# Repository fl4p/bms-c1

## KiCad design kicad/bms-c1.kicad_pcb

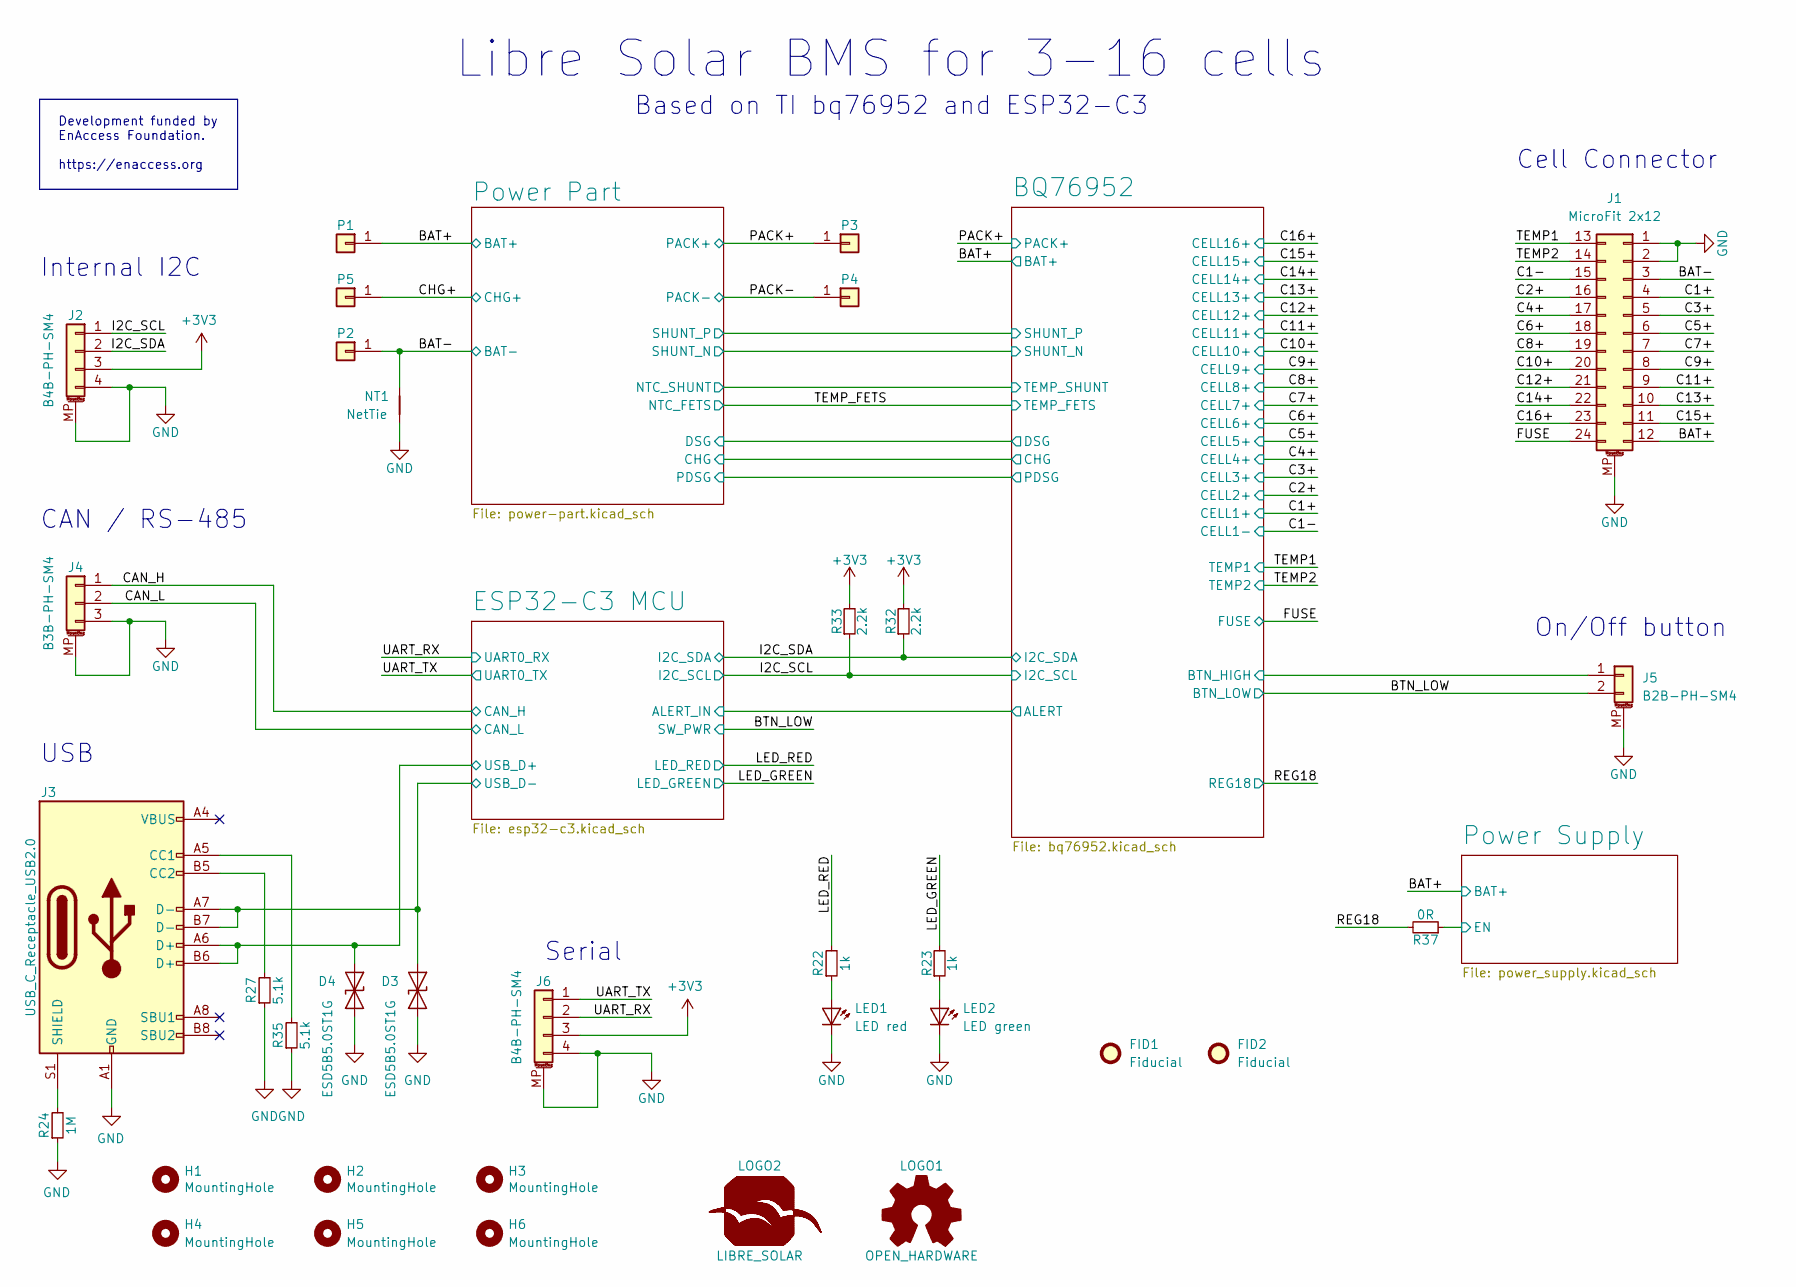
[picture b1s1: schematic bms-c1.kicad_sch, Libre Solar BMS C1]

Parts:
D3, D4: ESD5B5.0ST1G; D_SOD-523; PartNumber ESD5B5.0ST1G; LCSC C93623
FID1, FID2: Fiducial; Fiducial_1mm_Mask2mm
H1, H2, H3, H4, H5, H6: MountingHole; MountingHole_3.2mm_M3_Pad_TopBottom
J1: MicroFit 2x12; Molex_Micro-Fit_3.0_43045-2410_2x12-1MP_P3.00mm_Horizontal; PartNumber 662024231722
J2, J6: B4B-PH-SM4; JST_PH_B4B-PH-SM4-TB_1x04-1MP_P2.00mm_Vertical; PartNumber B4B-PH-SM4-TB(LF)(SN); LCSC C160354
J3: USB_C_Receptacle_USB2.0; USB_C_Receptacle_GCT_USB4105-xx-A_16P_TopMnt_Horizontal; PartNumber USB4105-GF-A
J4: B3B-PH-SM4; JST_PH_B3B-PH-SM4-TB_1x03-1MP_P2.00mm_Vertical; PartNumber B3B-PH-SM4-TB(LF)(SN); LCSC C160353
J5: B2B-PH-SM4; JST_PH_B2B-PH-SM4-TB_1x02-1MP_P2.00mm_Vertical; PartNumber B2B-PH-SM4-TB(LF)(SN); LCSC C160352
LED1: LED red; LED_0603_1608Metric; PartNumber LTST-C190KRKT; LCSC C94869
LED2: LED green; LED_0603_1608Metric; PartNumber LTST-C190KGKT; LCSC C125094
LOGO1: OPEN_HARDWARE; OSHW-Logo_5.7x6mm_SilkScreen
LOGO2: LIBRE_SOLAR; LIBRESOLAR_LOGO
NT1: NetTie; NetTie-2_SMD_Pad0.5mm
P1, P2, P3, P4: CONN_01X01; Wuerth_PowerPlus_M5_Nut; PartNumber 225852-E; LCSC C3217898
P5: CONN_01X01; SolderWirePad_1x01_SMD_5x10mm
R22, R23: 1k; R_0603_1608; PartNumber RC0603FR-071KL
R24: 1M; R_0603_1608; PartNumber RC0603FR-071ML
R27, R35: 5.1k; R_0603_1608; PartNumber RC0603FR-075K1L
R32, R33: 2.2k; R_0603_1608; PartNumber RC0603FR-072K2L
R37: 0R; R_0603_1608; PartNumber RC0603FR-070RL

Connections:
+3V3: J2.3, J6.3, R32.2, R33.2; also elsewhere on the board
/BAT+: J1.12, P1.1; also elsewhere on the board
/BAT-: J1.3, NT1.1, P2.1; also elsewhere on the board
/BQ76952/BTN_HIGH: J5.1; also elsewhere on the board
/BTN_LOW: J5.2; also elsewhere on the board
/C1+: J1.4; also elsewhere on the board
/C1-: J1.15; also elsewhere on the board
/C2+: J1.16; also elsewhere on the board
/C3+: J1.5; also elsewhere on the board
/C4+: J1.17; also elsewhere on the board
/C5+: J1.6; also elsewhere on the board
/C6+: J1.18; also elsewhere on the board
/C7+: J1.7; also elsewhere on the board
/C8+: J1.19; also elsewhere on the board
/C9+: J1.8; also elsewhere on the board
/C10+: J1.20; also elsewhere on the board
/C11+: J1.9; also elsewhere on the board
/C12+: J1.21; also elsewhere on the board
/C13+: J1.10; also elsewhere on the board
/C14+: J1.22; also elsewhere on the board
/C15+: J1.11; also elsewhere on the board
/C16+: J1.23; also elsewhere on the board
/CAN_H: J4.1; also elsewhere on the board
/CAN_L: J4.2; also elsewhere on the board
/CHG+: P5.1; also elsewhere on the board
/ESP32-C3 MCU/USB_D+: D4.2 (A2), J3.A6 (D+), J3.B6 (D+); also elsewhere on the board
/ESP32-C3 MCU/USB_D-: D3.2 (A2), J3.A7 (D-), J3.B7 (D-); also elsewhere on the board
/FUSE: J1.24; also elsewhere on the board
/I2C_SCL: J2.1, R33.1; also elsewhere on the board
/I2C_SDA: J2.2, R32.1; also elsewhere on the board
/LED_GREEN: R23.2; also elsewhere on the board
/LED_RED: R22.2; also elsewhere on the board
/PACK+: P3.1; also elsewhere on the board
/PACK-: P4.1; also elsewhere on the board
/Power Supply/EN: R37.1; also elsewhere on the board
/REG18: R37.2; also elsewhere on the board
/TEMP1: J1.13; also elsewhere on the board
/TEMP2: J1.14; also elsewhere on the board
/UART_RX: J6.2; also elsewhere on the board
/UART_TX: J6.1; also elsewhere on the board
GND: D3.1 (A1), D4.1 (A1), J1.1, J1.2, J1.MP (MountPin), J2.4, J2.MP (MountPin), J3.A1 (GND), J3.A12 (GND), J3.B1 (GND), J3.B12 (GND), J4.3, J4.MP (MountPin), J5.MP (MountPin), J6.4, J6.MP (MountPin), LED1.1 (K), LED2.1 (K), NT1.2, R24.1, R27.1, R35.1; also elsewhere on the board
unnamed: J3.A5 (CC1), R35.2
unnamed: J3.B5 (CC2), R27.2
unnamed: J3.S1 (SHIELD), R24.2
unnamed: LED1.2 (A), R22.1
unnamed: LED2.2 (A), R23.1

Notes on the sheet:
Based on TI bq76952 and ESP32-C3
CAN / RS-485
Development funded by EnAccess Foundation. https://enaccess.org
USB
Serial
Libre Solar BMS for 3-16 cells
Cell Connector
Internal I2C
On/Off button

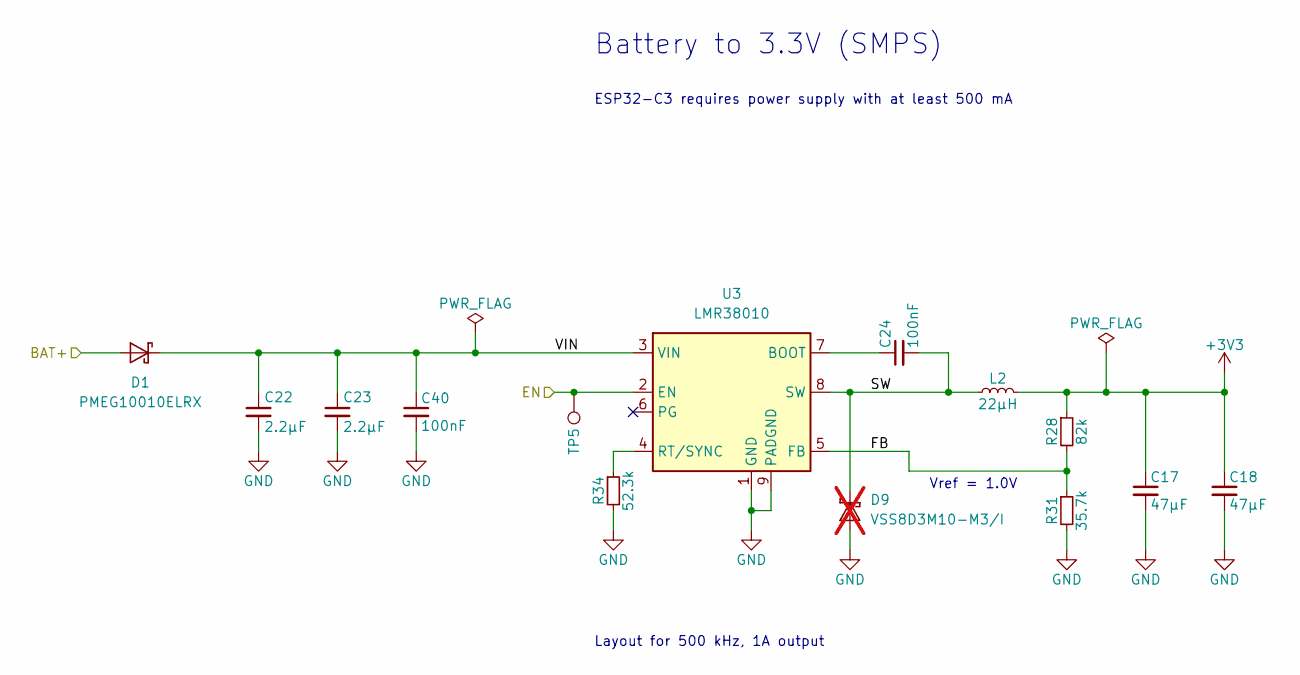
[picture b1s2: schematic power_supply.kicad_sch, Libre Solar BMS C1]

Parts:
C17, C18: 47µF; C_1210_3225; PartNumber CL32B476MPJNNNE; LCSC C525654
C22, C23: 2.2µF; C_1210_3225; PartNumber CL32B225KCJSNNE; LCSC C55151
C24, C40: 100nF; C_0603_1608; PartNumber CL10B104KC8NNNC; LCSC C15725
D1: PMEG10010ELRX; D_SOD-123F; PartNumber PMEG10010ELRX; LCSC C179426
D9: VSS8D3M10-M3/I; D_SOD-128; PartNumber VSS8D3M10-M3/H; LCSC C3760174; not fitted
L2: 22µH; Bourns_SRN8040TA; PartNumber SRN8040-220M; LCSC C92946
R28: 82k; R_0603_1608; PartNumber RC0603FR-0782KL
R31: 35.7k; R_0603_1608; PartNumber RC0603FR-0735K7L
R34: 52.3k; R_0603_1608; PartNumber RC0603FR-0752K3L
TP5: TestPoint; TestPoint_Pad_D1.5mm
U3: LMR38010; SOIC-8-1EP_3.9x4.9mm_P1.27mm_EP2.4x3.1mm_ThermalVias; PartNumber LMR38010SDDAR; LCSC C3192337

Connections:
+3V3: C17.1, C18.1, L2.2, R28.1; also elsewhere on the board
/BAT+: D1.2 (A); also elsewhere on the board
/Power Supply/EN: TP5.1, U3.2 (EN); also elsewhere on the board
/Power Supply/FB: R28.2, R31.1, U3.5 (FB)
/Power Supply/SW: C24.2, D9.1 (K), L2.1, U3.8 (SW)
/Power Supply/VIN: C22.1, C23.1, C40.1, D1.1 (K), U3.3 (VIN)
GND: C17.2, C18.2, C22.2, C23.2, C40.2, D9.2 (A), R31.2, R34.2, U3.1 (GND), U3.9 (PADGND); also elsewhere on the board
unnamed: C24.1, U3.7 (BOOT)
unnamed: R34.1, U3.4 (RT/SYNC)

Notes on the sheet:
ESP32-C3 requires power supply with at least 500 mA
Layout for 500 kHz, 1A output
Battery to 3.3V (SMPS)
Vref = 1.0V

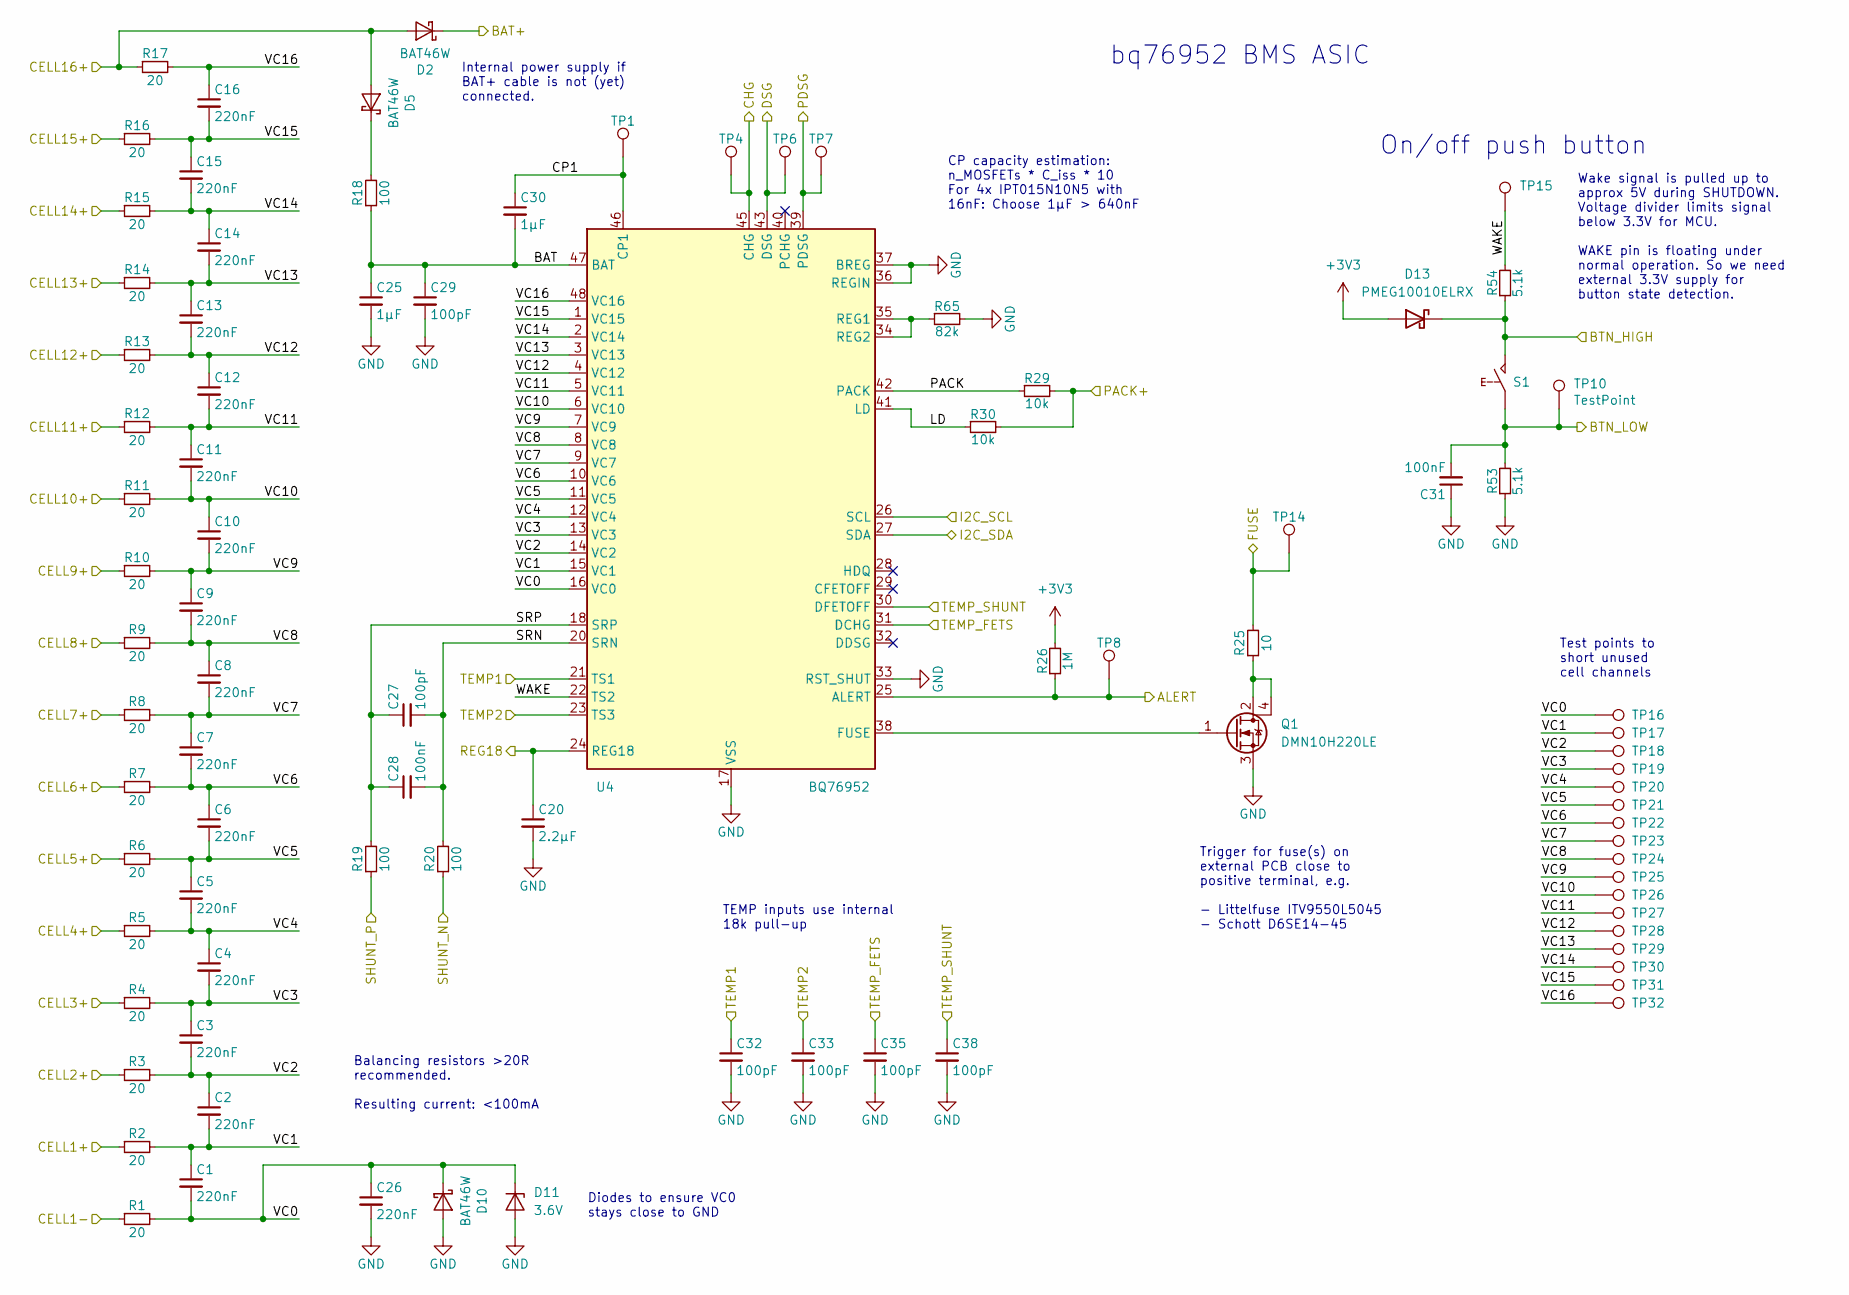
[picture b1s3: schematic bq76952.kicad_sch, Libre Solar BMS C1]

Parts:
C1, C2, C3, C4, C5, C6, C7, C8, C9, C10, C11, C12, C13, C14, C15, C16, C26: 220nF; C_0603_1608; PartNumber CL10B224KA8NNNC; LCSC C21120
C20: 2.2µF; C_0603_1608; PartNumber CL10A225KP8NNNC; LCSC C1607
C25: 1µF; C_1206_3216; PartNumber CL31B105KCHNNNE; LCSC C13832
C27, C29, C32, C33, C35, C38: 100pF; C_0603_1608; PartNumber CL10C101JC8NNNC; LCSC C296717
C28, C31: 100nF; C_0603_1608; PartNumber CL10B104KC8NNNC; LCSC C15725
C30: 1µF; C_0603_1608; PartNumber CL10A105KA8NNNC; LCSC C5673
D2, D5, D10: BAT46W; D_SOD-123; PartNumber BAT46W-7-F; LCSC C83152
D11: 3.6V; D_SOD-123; PartNumber MMSZ4685T1G; LCSC C66886
D13: PMEG10010ELRX; D_SOD-123F; PartNumber PMEG10010ELRX; LCSC C179426
Q1: DMN10H220LE; SOT-223; PartNumber DMN10H220LE; LCSC C258216
R1, R2, R3, R4, R5, R6, R7, R8, R9, R10, R11, R12, R13, R14, R15, R16, R17: 20; R_2010_5025; PartNumber RC2010JK-0720RL; LCSC C163344
R18: 100; R_1206_3216; PartNumber RC1206FR-07100RL
R19, R20: 100; R_0603_1608; PartNumber RC0603FR-07100RL
R25: 10; R_1206_3216; PartNumber RC1206FR-0710RL
R26: 1M; R_0603_1608; PartNumber RC0603FR-071ML
R29, R30: 10k; R_0603_1608; PartNumber RC0603FR-0710KL
R53, R54: 5.1k; R_0603_1608; PartNumber RC0603FR-075K1L
R65: 82k; R_0603_1608; PartNumber RC0603FR-0782KL
S1: SW_PUSH; SW_SPST_TL3305A; PartNumber TL3305AF160QG; LCSC C2886899
TP1, TP4, TP6, TP7, TP8, TP10, TP14, TP15: TestPoint; TestPoint_Pad_D1.5mm
TP16, TP17, TP18, TP19, TP20, TP21, TP22, TP23, TP24, TP25, TP26, TP27, TP28, TP29, TP30, TP31, TP32: TestPoint; TestPoint_Pad_1.0x1.0mm
U4: BQ76952; TQFP-48_7x7mm_P0.5mm; PartNumber BQ76952PFBR; LCSC C2862742

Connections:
+3V3: D13.2 (A), R26.2; also elsewhere on the board
/BAT+: D2.1 (K); also elsewhere on the board
/BQ76952/ALERT: R26.1, TP8.1, U4.25 (ALERT); also elsewhere on the board
/BQ76952/BAT: C25.1, C29.1, C30.2, R18.1, U4.47 (BAT)
/BQ76952/BTN_HIGH: D13.1 (K), R54.1, S1.2; also elsewhere on the board
/BQ76952/CHG: TP4.1, U4.45 (CHG); also elsewhere on the board
/BQ76952/CP1: C30.1, TP1.1, U4.46 (CP1)
/BQ76952/DSG: TP6.1, U4.43 (DSG); also elsewhere on the board
/BQ76952/LD: R30.1, U4.41 (LD)
/BQ76952/PACK: R29.1, U4.42 (PACK)
/BQ76952/PDSG: TP7.1, U4.39 (PDSG); also elsewhere on the board
/BQ76952/SHUNT_N: R20.1; also elsewhere on the board
/BQ76952/SHUNT_P: R19.1; also elsewhere on the board
/BQ76952/SRN: C27.2, C28.2, R20.2, U4.20 (SRN)
/BQ76952/SRP: C27.1, C28.1, R19.2, U4.18 (SRP)
/BQ76952/TEMP_SHUNT: C38.1, U4.30 (DFETOFF); also elsewhere on the board
/BQ76952/VC0: C1.2, C26.1, D10.1 (K), D11.1 (K), R1.2, TP16.1, U4.16 (VC0)
/BQ76952/VC1: C1.1, C2.2, R2.2, TP17.1, U4.15 (VC1)
/BQ76952/VC2: C2.1, C3.2, R3.2, TP18.1, U4.14 (VC2)
/BQ76952/VC3: C3.1, C4.2, R4.2, TP19.1, U4.13 (VC3)
/BQ76952/VC4: C4.1, C5.2, R5.2, TP20.1, U4.12 (VC4)
/BQ76952/VC5: C5.1, C6.2, R6.2, TP21.1, U4.11 (VC5)
/BQ76952/VC6: C6.1, C7.2, R7.2, TP22.1, U4.10 (VC6)
/BQ76952/VC7: C7.1, C8.2, R8.2, TP23.1, U4.9 (VC7)
/BQ76952/VC8: C8.1, C9.2, R9.2, TP24.1, U4.8 (VC8)
/BQ76952/VC9: C9.1, C10.2, R10.2, TP25.1, U4.7 (VC9)
/BQ76952/VC10: C10.1, C11.2, R11.2, TP26.1, U4.6 (VC10)
/BQ76952/VC11: C11.1, C12.2, R12.2, TP27.1, U4.5 (VC11)
/BQ76952/VC12: C12.1, C13.2, R13.2, TP28.1, U4.4 (VC12)
/BQ76952/VC13: C13.1, C14.2, R14.2, TP29.1, U4.3 (VC13)
/BQ76952/VC14: C14.1, C15.2, R15.2, TP30.1, U4.2 (VC14)
/BQ76952/VC15: C15.1, C16.2, R16.2, TP31.1, U4.1 (VC15)
/BQ76952/VC16: C16.1, R17.2, TP32.1, U4.48 (VC16)
/BQ76952/WAKE: R54.2, TP15.1, U4.22 (TS2)
/BTN_LOW: C31.2, R53.2, S1.1, TP10.1; also elsewhere on the board
/C1+: R2.1; also elsewhere on the board
/C1-: R1.1; also elsewhere on the board
/C2+: R3.1; also elsewhere on the board
/C3+: R4.1; also elsewhere on the board
/C4+: R5.1; also elsewhere on the board
/C5+: R6.1; also elsewhere on the board
/C6+: R7.1; also elsewhere on the board
/C7+: R8.1; also elsewhere on the board
/C8+: R9.1; also elsewhere on the board
/C9+: R10.1; also elsewhere on the board
/C10+: R11.1; also elsewhere on the board
/C11+: R12.1; also elsewhere on the board
/C12+: R13.1; also elsewhere on the board
/C13+: R14.1; also elsewhere on the board
/C14+: R15.1; also elsewhere on the board
/C15+: R16.1; also elsewhere on the board
/C16+: D2.2 (A), D5.2 (A), R17.1; also elsewhere on the board
/FUSE: R25.2, TP14.1; also elsewhere on the board
/I2C_SCL: U4.26 (SCL); also elsewhere on the board
/I2C_SDA: U4.27 (SDA); also elsewhere on the board
/PACK+: R29.2, R30.2; also elsewhere on the board
/REG18: C20.1, U4.24 (REG18); also elsewhere on the board
/TEMP1: C32.1, U4.21 (TS1); also elsewhere on the board
/TEMP2: C33.1, U4.23 (TS3); also elsewhere on the board
/TEMP_FETS: C35.1, U4.31 (DCHG); also elsewhere on the board
GND: C20.2, C25.2, C26.2, C29.2, C31.1, C32.2, C33.2, C35.2, C38.2, D10.2 (A), D11.2 (A), Q1.3 (S), R53.1, R65.2, U4.17 (VSS), U4.33 (RST_SHUT), U4.36 (REGIN), U4.37 (BREG); also elsewhere on the board
unnamed: D5.1 (K), R18.2
unnamed: Q1.2 (D), Q1.4 (D), R25.1
unnamed: Q1.1 (G), U4.38 (FUSE)
unnamed: R65.1, U4.34 (REG2), U4.35 (REG1)

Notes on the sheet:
TEMP inputs use internal 18k pull-up
CP capacity estimation: n_MOSFETs * C_iss * 10 For 4x IPT015N10N5 with 16nF: Choose 1µF > 640nF
bq76952 BMS ASIC
Wake signal is pulled up to approx 5V during SHUTDOWN. Voltage divider limits signal below 3.3V for MCU. WAKE pin is floating under normal operation. So we need external 3.3V supply for button state detection.
On/off push button
Trigger for fuse(s) on external PCB close to positive terminal, e.g. - Littelfuse ITV9550L5045 - Schott D6SE14-45
Balancing resistors >20R recommended. Resulting current: <100mA
Test points to short unused cell channels
Internal power supply if BAT+ cable is not (yet) connected.
Diodes to ensure VC0 stays close to GND

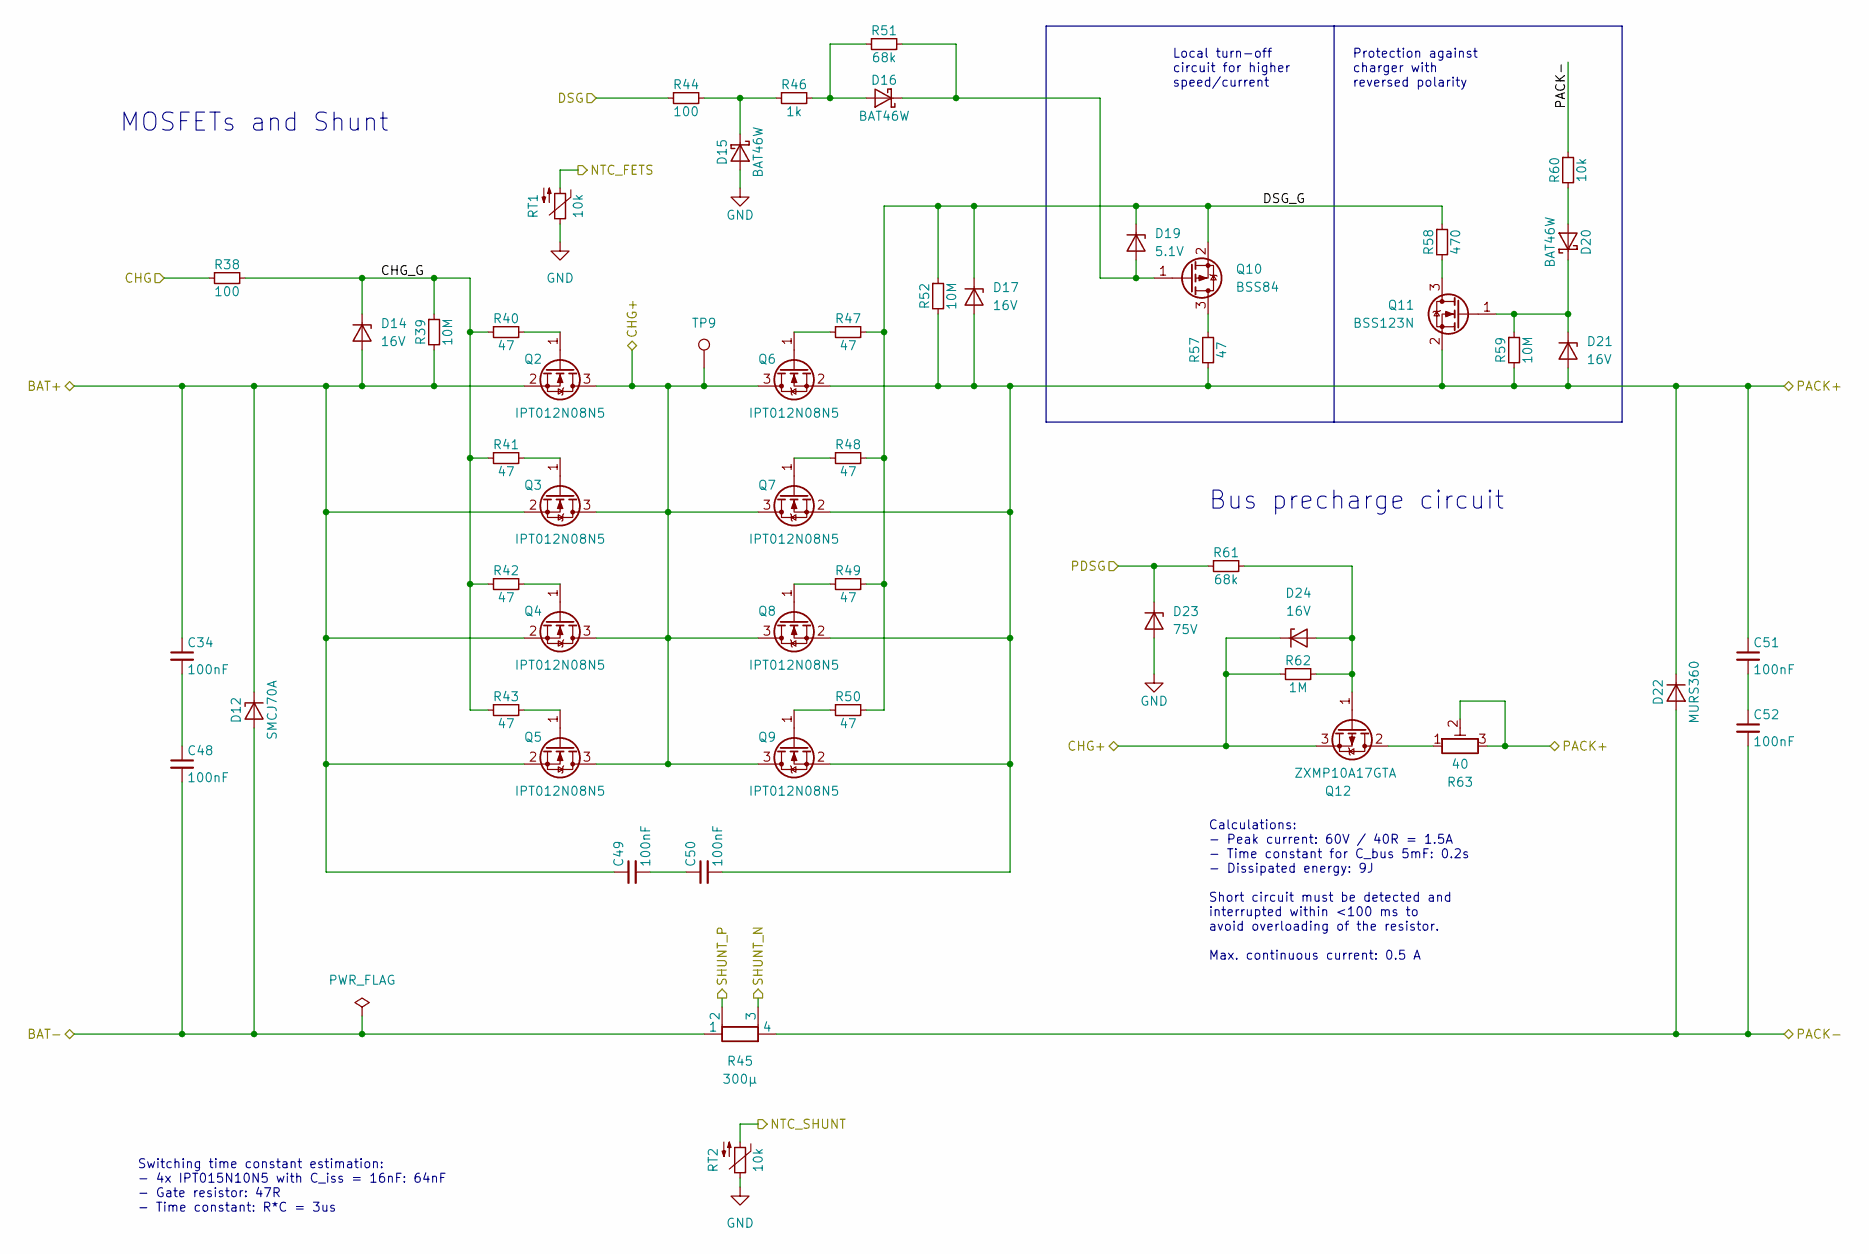
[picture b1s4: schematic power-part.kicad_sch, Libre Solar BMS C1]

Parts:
C34, C48, C49, C50, C51, C52: 100nF; C_0603_1608; PartNumber CL10B104KC8NNNC; LCSC C15725
D12: SMCJ70A; D_SMC; PartNumber SMCJ70A; LCSC C135194
D14, D17, D21, D24: 16V; D_SOD-123; PartNumber MMSZ5246B-7-F; LCSC C282317
D15, D16, D20: BAT46W; D_SOD-123; PartNumber BAT46W-7-F; LCSC C83152
D19: 5.1V; D_SOD-323; PartNumber BZT52C5V1S-7-F; LCSC C151348
D22: MURS360; D_SMC; PartNumber MURS360; LCSC C388245
D23: 75V; D_SOD-123; PartNumber MMSZ5267BT1G; LCSC C266795
Q2, Q3, Q4, Q5, Q6, Q7, Q8, Q9: IPT012N08N5; Infineon_PG-HSOF-8-1_ThermalVias; PartNumber IPT012N08N5; LCSC C531199
Q10: BSS84; SOT-23; PartNumber BSS84AK,215; LCSC C127273
Q11: BSS123N; SOT-23; PartNumber BSS123N H6327; LCSC C534594
Q12: ZXMP10A17GTA; SOT-223-3_TabPin2; PartNumber ZXMP10A17GTA; LCSC C32998
R38, R44: 100; R_0603_1608; PartNumber RC0603FR-07100RL
R39, R52, R59: 10M; R_0603_1608; PartNumber RC0603FR-0710ML
R40, R41, R42, R43, R47, R48, R49, R50, R57: 47; R_0603_1608; PartNumber RC0603FR-0747RL
R45: 300µ; R_Shunt_5931_Kelvin; PartNumber WSLP5931L3000FEA
R46: 1k; R_0603_1608; PartNumber RC0603FR-071KL
R51, R61: 68k; R_0603_1608; PartNumber RC0603FR-0768KL
R58: 470; R_0603_1608; PartNumber RC0603FR-07470RL
R60: 10k; R_0603_1608; PartNumber RC0603FR-0710KL
R62: 1M; R_0603_1608; PartNumber RC0603FR-071ML
R63: 40; Bourns_PWR163; PartNumber PWR163S-25-40R0FE
RT1, RT2: 10k; R_0603_1608; PartNumber NTCG163JF103FT1S; LCSC C406719
TP9: TestPoint; TestPoint_Pad_D1.5mm

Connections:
/BAT+: C34.1, C49.1, D12.1 (K), D14.2 (A), Q2.2 (S), Q3.2 (S), Q4.2 (S), Q5.2 (S), R39.2; also elsewhere on the board
/BAT-: C48.2, D12.2 (A), R45.1; also elsewhere on the board
/BQ76952/CHG: R38.1; also elsewhere on the board
/BQ76952/DSG: R44.1; also elsewhere on the board
/BQ76952/PDSG: D23.1 (K), R61.1; also elsewhere on the board
/BQ76952/SHUNT_N: R45.3; also elsewhere on the board
/BQ76952/SHUNT_P: R45.2; also elsewhere on the board
/BQ76952/TEMP_SHUNT: RT2.2; also elsewhere on the board
/CHG+: D24.1 (K), Q2.3 (D), Q3.3 (D), Q4.3 (D), Q5.3 (D), Q6.3 (D), Q7.3 (D), Q8.3 (D), Q9.3 (D), Q12.3 (S), R62.1, TP9.1; also elsewhere on the board
/PACK+: C50.2, C51.1, D17.2 (A), D21.2 (A), D22.1 (K), Q6.2 (S), Q7.2 (S), Q8.2 (S), Q9.2 (S), Q11.2 (S), R52.2, R57.1, R59.2, R63.2, R63.3; also elsewhere on the board
/PACK-: C52.2, D22.2 (A), R45.4, R60.1; also elsewhere on the board
/Power Part/CHG_G: D14.1 (K), R38.2, R39.1, R40.1, R41.1, R42.1, R43.1
/Power Part/DSG_G: D17.1 (K), D19.1 (K), Q10.2 (S), R47.2, R48.2, R49.2, R50.2, R52.1, R58.1
/TEMP_FETS: RT1.2; also elsewhere on the board
GND: D15.2 (A), D23.2 (A), RT1.1, RT2.1; also elsewhere on the board
unnamed: C34.2, C48.1
unnamed: C49.2, C50.1
unnamed: C51.2, C52.1
unnamed: D15.1 (K), R44.2, R46.1
unnamed: D16.2 (A), R46.2, R51.1
unnamed: D16.1 (K), D19.2 (A), Q10.1 (G), R51.2
unnamed: D20.2 (A), R60.2
unnamed: D20.1 (K), D21.1 (K), Q11.1 (G), R59.1
unnamed: D24.2 (A), Q12.1 (G), R61.2, R62.2
unnamed: Q2.1 (G), R40.2
unnamed: Q3.1 (G), R41.2
unnamed: Q4.1 (G), R42.2
unnamed: Q5.1 (G), R43.2
unnamed: Q6.1 (G), R47.1
unnamed: Q7.1 (G), R48.1
unnamed: Q8.1 (G), R49.1
unnamed: Q9.1 (G), R50.1
unnamed: Q10.3 (D), R57.2
unnamed: Q11.3 (D), R58.2
unnamed: Q12.2 (D), R63.1

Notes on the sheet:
Protection against charger with reversed polarity
Switching time constant estimation: - 4x IPT015N10N5 with C_iss = 16nF: 64nF - Gate resistor: 47R - Time constant: R*C = 3us
MOSFETs and Shunt
Local turn-off circuit for higher speed/current
Bus precharge circuit
Calculations: - Peak current: 60V / 40R = 1.5A - Time constant for C_bus 5mF: 0.2s - Dissipated energy: 9J Short circuit must be detected and interrupted within <100 ms to avoid overloading of the resistor. Max. continuous current: 0.5 A

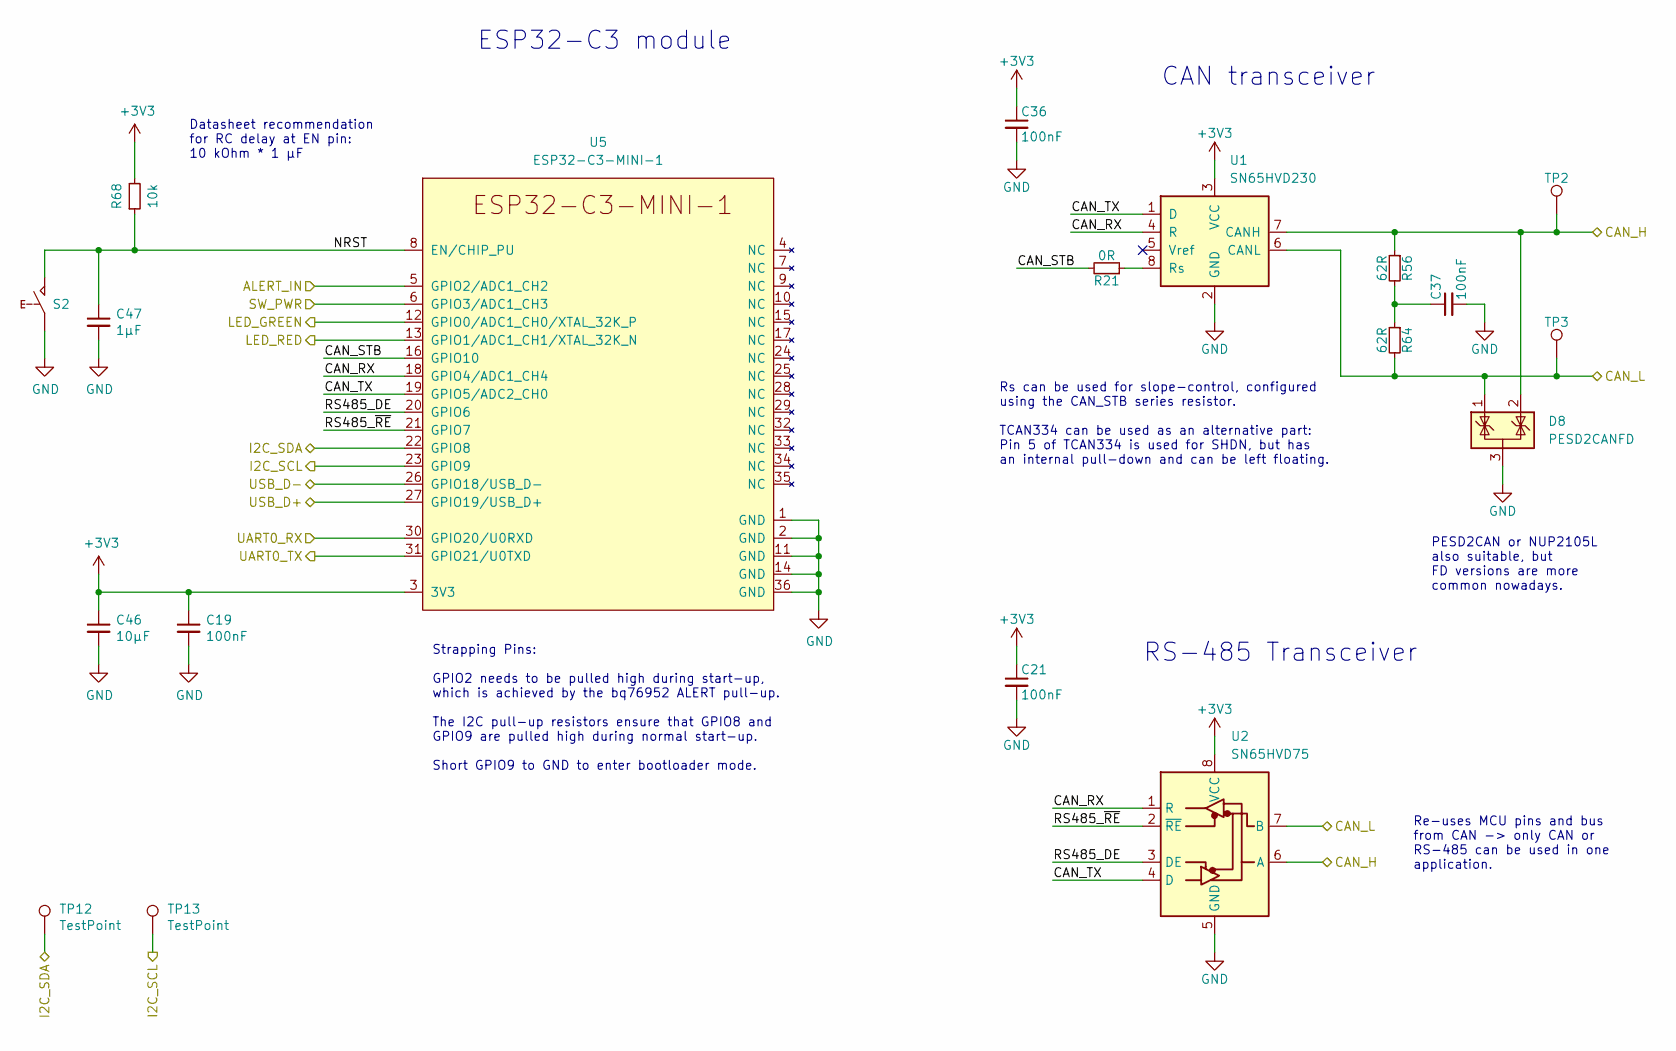
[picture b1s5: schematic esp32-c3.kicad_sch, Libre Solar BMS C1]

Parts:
C19, C21, C36, C37: 100nF; C_0603_1608; PartNumber CL10B104KC8NNNC; LCSC C15725
C46: 10µF; C_0805_2012; PartNumber CL21A106KPFNNNE; LCSC C17024
C47: 1µF; C_0603_1608; PartNumber CL10A105KA8NNNC; LCSC C5673
D8: PESD2CANFD; SOT-23; PartNumber PESD2CANFD24V-TR; LCSC C552486
R21: 0R; R_0603_1608; PartNumber RC0603FR-070RL
R56, R64: 62R; R_0603_1608; PartNumber RC0603FR-0762RL
R68: 10k; R_0603_1608; PartNumber RC0603FR-0710KL
S2: SW_PUSH; SW_SPST_TL3305A; PartNumber TL3305AF160QG; LCSC C2886899
TP2, TP3, TP12, TP13: TestPoint; TestPoint_Pad_D1.5mm
U1: SN65HVD230; SOIC-8_3.9x4.9mm_P1.27mm; PartNumber SN65HVD230DR; LCSC C12084
U2: SN65HVD75; SOIC-8_3.9x4.9mm_P1.27mm; PartNumber SN65HVD75DR; LCSC C57928
U5: ESP32-C3-MINI-1; PartNumber ESP32-C3-MINI-1-N4; LCSC C2838502

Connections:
+3V3: C19.1, C21.1, C36.1, C46.1, R68.2, U1.3 (VCC), U2.8 (VCC), U5.3 (3V3); also elsewhere on the board
/BQ76952/ALERT: U5.5 (GPIO2/ADC1_CH2); also elsewhere on the board
/BTN_LOW: U5.6 (GPIO3/ADC1_CH3); also elsewhere on the board
/CAN_H: D8.2 (K), R56.1, TP2.1, U1.7 (CANH), U2.6 (A); also elsewhere on the board
/CAN_L: D8.1 (K), R64.2, TP3.1, U1.6 (CANL), U2.7 (B); also elsewhere on the board
/ESP32-C3 MCU/CAN_RX: U1.4 (R), U2.1 (R), U5.18 (GPIO4/ADC1_CH4)
/ESP32-C3 MCU/CAN_STB: R21.2, U5.16 (GPIO10)
/ESP32-C3 MCU/CAN_TX: U1.1 (D), U2.4 (D), U5.19 (GPIO5/ADC2_CH0)
/ESP32-C3 MCU/NRST: C47.1, R68.1, S2.2, U5.8 (EN/CHIP_PU)
/ESP32-C3 MCU/RS485_DE: U2.3 (DE), U5.20 (GPIO6)
/ESP32-C3 MCU/RS485_~RE: U2.2 (~RE), U5.21 (GPIO7)
/ESP32-C3 MCU/USB_D+: U5.27 (GPIO19/USB_D+); also elsewhere on the board
/ESP32-C3 MCU/USB_D-: U5.26 (GPIO18/USB_D-); also elsewhere on the board
/I2C_SCL: TP13.1, U5.23 (GPIO9); also elsewhere on the board
/I2C_SDA: TP12.1, U5.22 (GPIO8); also elsewhere on the board
/LED_GREEN: U5.12 (GPIO0/ADC1_CH0/XTAL_32K_P); also elsewhere on the board
/LED_RED: U5.13 (GPIO1/ADC1_CH1/XTAL_32K_N); also elsewhere on the board
/UART_RX: U5.30 (GPIO20/U0RXD); also elsewhere on the board
/UART_TX: U5.31 (GPIO21/U0TXD); also elsewhere on the board
GND: C19.2, C21.2, C36.2, C37.2, C46.2, C47.2, D8.3 (A), S2.1, U1.2 (GND), U2.5 (GND), U5.1 (GND), U5.2 (GND), U5.11 (GND), U5.14 (GND), U5.36 (GND); also elsewhere on the board
unnamed: C37.1, R56.2, R64.1
unnamed: R21.1, U1.8 (Rs)

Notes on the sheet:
Datasheet recommendation for RC delay at EN pin: 10 kOhm * 1 µF
Strapping Pins: GPIO2 needs to be pulled high during start-up, which is achieved by the bq76952 ALERT pull-up. The I2C pull-up resistors ensure that GPIO8 and GPIO9 are pulled high during normal start-up. Short GPIO9 to GND to enter bootloader mode.
RS-485 Transceiver
Re-uses MCU pins and bus from CAN -> only CAN or RS-485 can be used in one application.
PESD2CAN or NUP2105L also suitable, but FD versions are more common nowadays.
CAN transceiver
ESP32-C3 module
Rs can be used for slope-control, configured using the CAN_STB series resistor. TCAN334 can be used as an alternative part: Pin 5 of TCAN334 is used for SHDN, but has an internal pull-down and can be left floating.

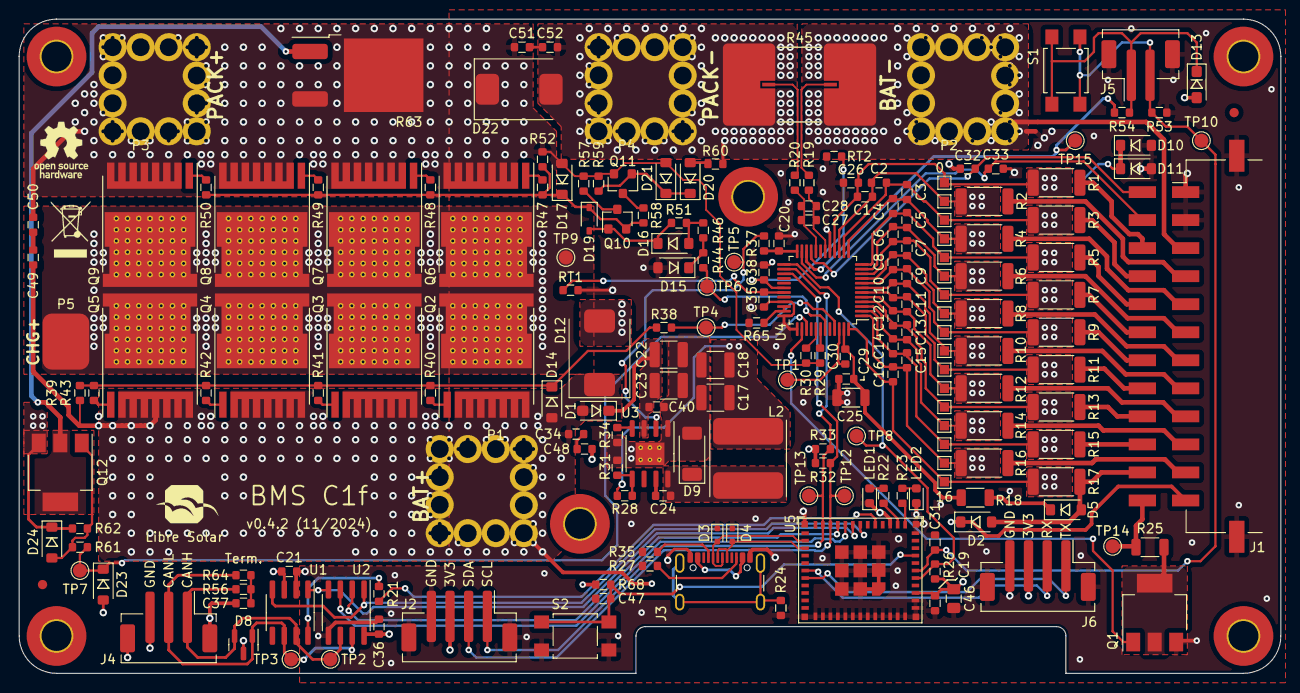
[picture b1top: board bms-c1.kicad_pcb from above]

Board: 4 copper layers, 135.0 x 70.0 mm, 208 parts (0 on the bottom side), 117 nets.

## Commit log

2024-11-30 power terminals THT, add mask

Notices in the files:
kicad/bms-c1.kicad_pcb:
License: CERN-OHL-W
